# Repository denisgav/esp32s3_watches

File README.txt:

useful links:
https://mischianti.org/vcc-gnd-studio-yd-esp32-s3-devkitc-1-clone-high-resolution-pinout-and-specs/
https://github.com/rtek1000/YD-ESP32-23

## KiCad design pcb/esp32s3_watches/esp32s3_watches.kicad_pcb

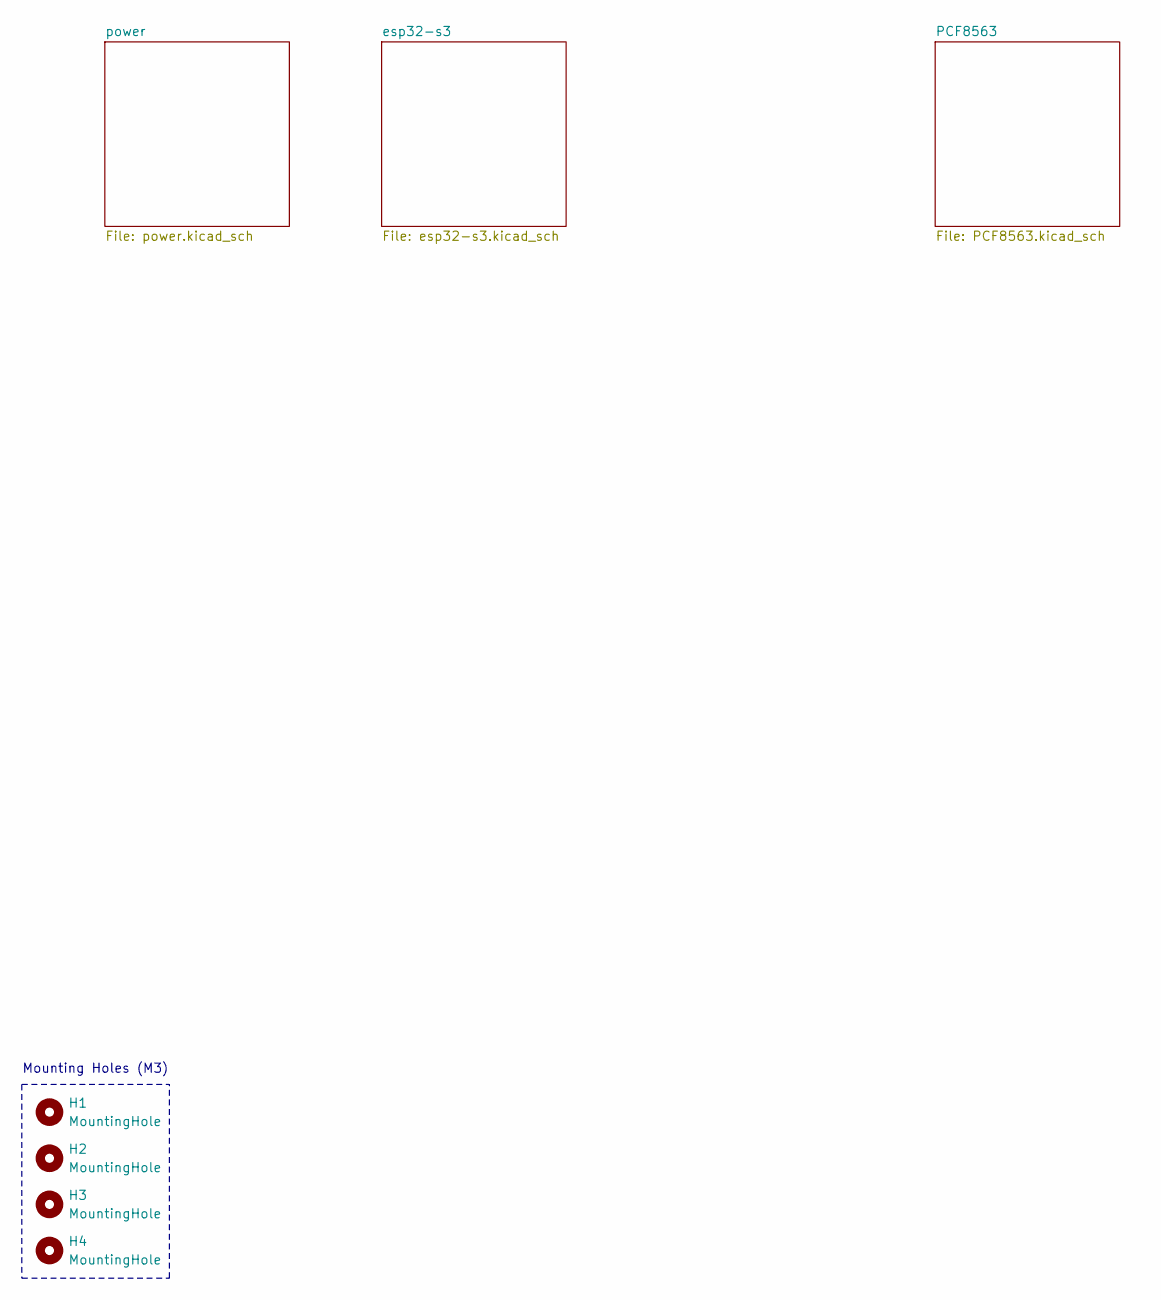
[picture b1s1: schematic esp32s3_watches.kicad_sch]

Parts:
H1, H2, H3, H4: MountingHole; MountingHole_3.2mm_M3

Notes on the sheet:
Mounting Holes (M3)

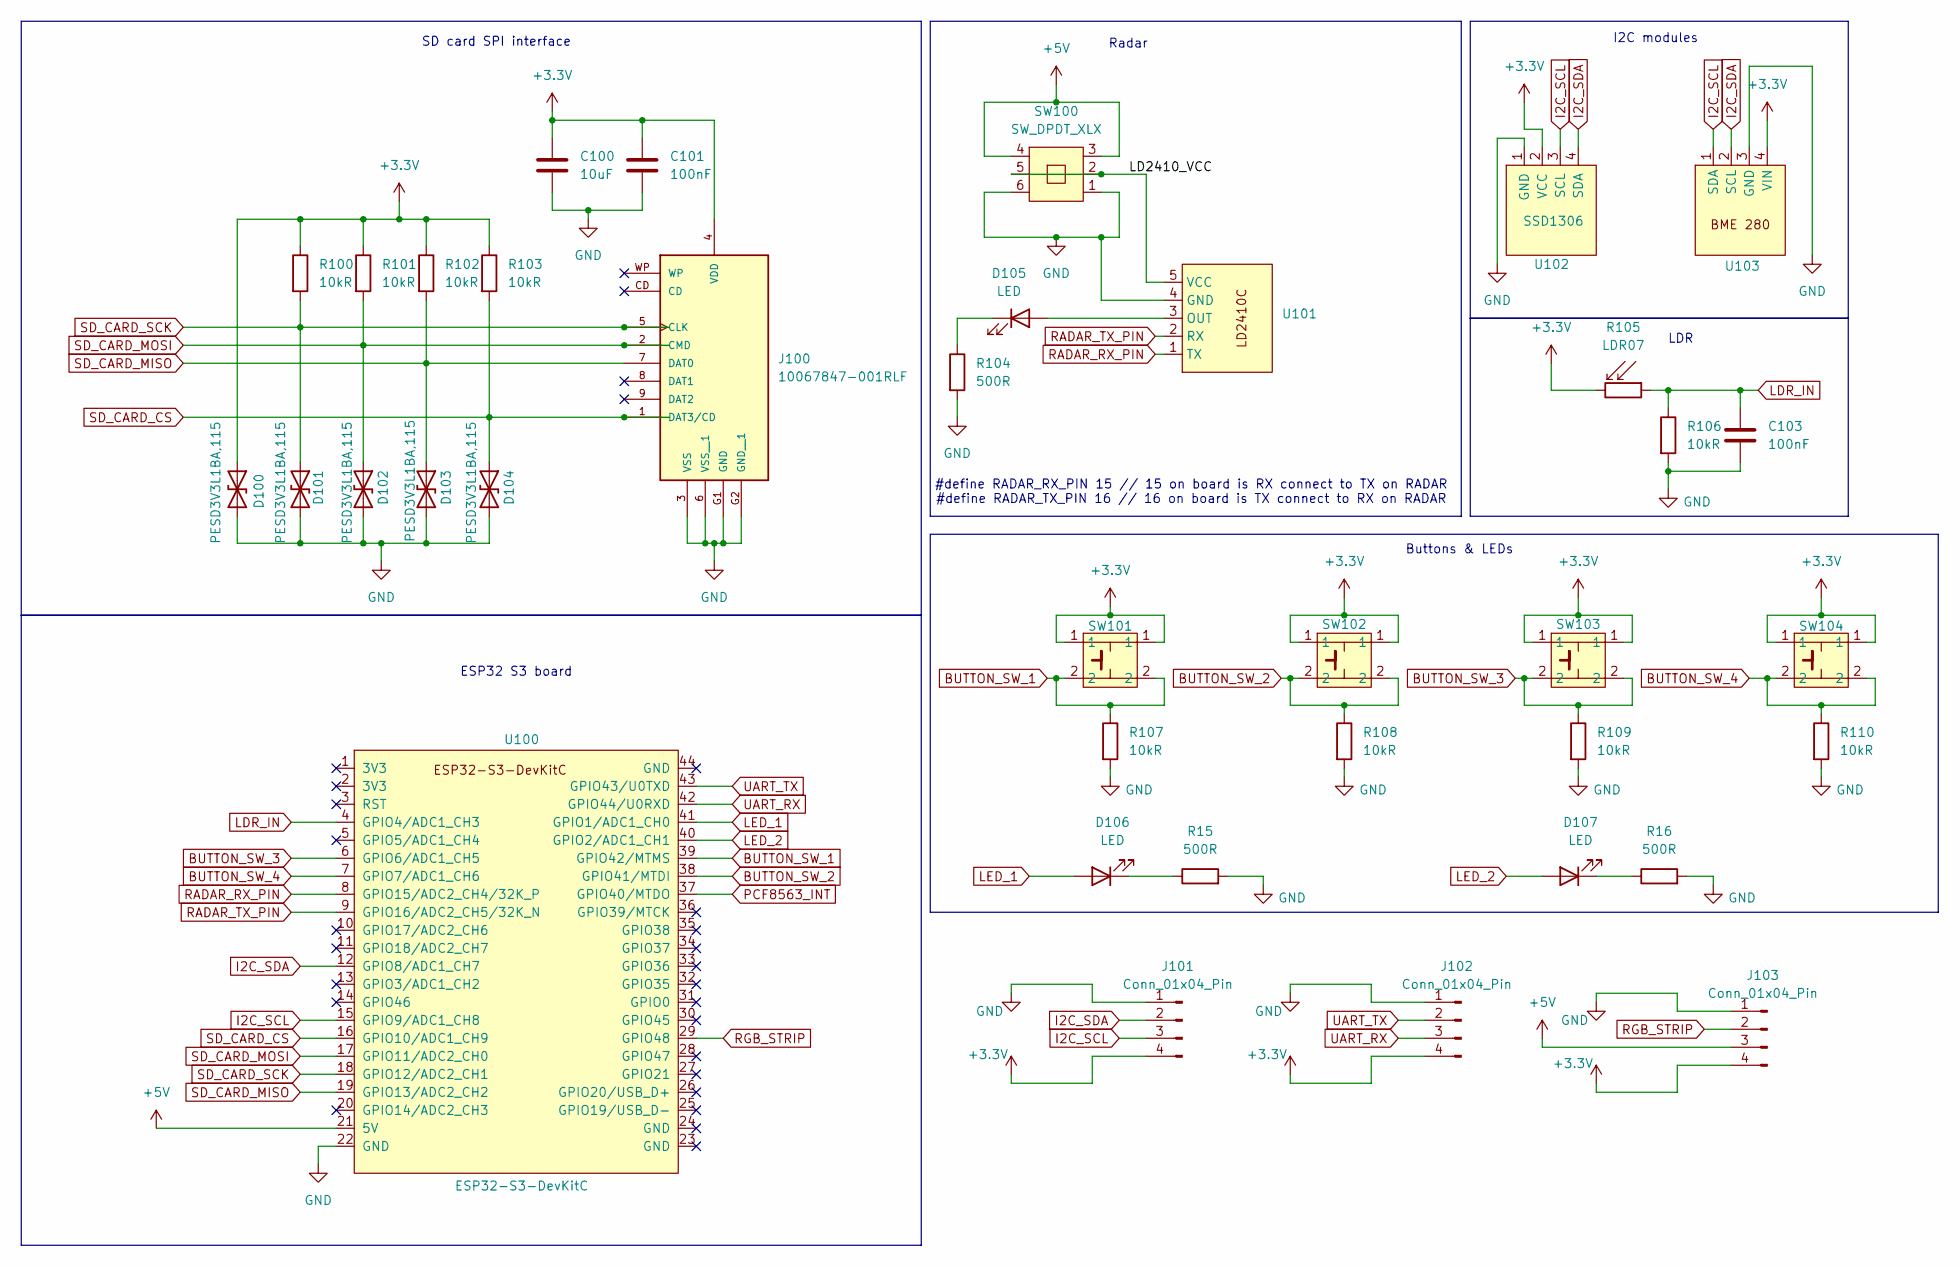
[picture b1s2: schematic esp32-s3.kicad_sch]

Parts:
C100: 10uF; C_0805_2012Metric
C101, C103: 100nF; C_0603_1608Metric
D100, D101, D102, D103, D104: PESD3V3L1BA,115; D_SOD-323; DigiKey Part Number 1727-3825-6-ND
D105, D106, D107: LED; LED_D5.0mm
J100: 10067847-001RLF; AMPHENOL_10067847-001RLF; PARTREV K
J101, J102, J103: Conn_01x04_Pin; PinHeader_1x04_P2.54mm_Vertical
R15, R16, R104: 500R; R_0805_2012Metric
R100, R101, R102, R103, R106, R107, R108, R109, R110: 10kR; R_0805_2012Metric
R105: LDR07; R_LDR_5.1x4.3mm_P3.4mm_Vertical
SW100: SW_DPDT_XLX
SW101, SW102, SW103, SW104: SW_PUSH_6mm_H5mm
U100: ESP32-S3-DevKitC
U101: LD2410C
U102: SSD1306; 128x64OLED
U103: BME280

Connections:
+3.3V: C100.1, C101.1, D100.1 (A1), J100.4 (VDD), J101.4, J102.4, J103.4, R100.1, R101.1, R102.1, R103.1, R105.2, SW101.1, SW102.1, SW103.1, SW104.1, U102.2 (VCC), U103.4 (VIN); also elsewhere on the board
+5V: J103.3, SW100.3, SW100.4, U100.21 (5V); also elsewhere on the board
/esp32-s3/LD2410_VCC: SW100.2, SW100.5, U101.5 (VCC)
BUTTON_SW_1: R107.1, SW101.2, U100.39 (GPIO42/MTMS)
BUTTON_SW_2: R108.1, SW102.2, U100.38 (GPIO41/MTDI)
BUTTON_SW_3: R109.1, SW103.2, U100.6 (GPIO6/ADC1_CH5)
BUTTON_SW_4: R110.1, SW104.2, U100.7 (GPIO7/ADC1_CH6)
GND: C100.2, C101.2, C103.2, D100.2 (A2), D101.2 (A2), D102.2 (A2), D103.2 (A2), D104.2 (A2), J100.3 (VSS), J100.6 (VSS__1), J100.G1 (GND), J100.G2 (GND__1), J101.1, J102.1, J103.1, R15.2, R16.2, R104.2, R106.2, R107.2, R108.2, R109.2, R110.2, SW100.1, SW100.6, U100.22 (GND), U101.4 (GND), U102.1 (GND), U103.3 (GND); also elsewhere on the board
I2C_SCL: J101.3, U100.15 (GPIO9/ADC1_CH8), U102.3 (SCL), U103.1 (SDA); also elsewhere on the board
I2C_SDA: J101.2, U100.12 (GPIO8/ADC1_CH7), U102.4 (SDA), U103.2 (SCL); also elsewhere on the board
LDR_IN: C103.1, R105.1, R106.1, U100.4 (GPIO4/ADC1_CH3)
LED_1: D106.2 (A), U100.41 (GPIO1/ADC1_CH0)
LED_2: D107.2 (A), U100.40 (GPIO2/ADC1_CH1)
unnamed: D105.2 (A), U101.3 (OUT)
unnamed: D105.1 (K), R104.1
unnamed: D106.1 (K), R15.1
unnamed: D107.1 (K), R16.1
PCF8563_INT: U100.37 (GPIO40/MTDO); also elsewhere on the board
RADAR_RX_PIN: U100.8 (GPIO15/ADC2_CH4/32K_P), U101.1 (TX)
RADAR_TX_PIN: U100.9 (GPIO16/ADC2_CH5/32K_N), U101.2 (RX)
RGB_STRIP: J103.2, U100.29 (GPIO48)
SD_CARD_CS: D104.1 (A1), J100.1 (DAT3/CD), R103.2, U100.16 (GPIO10/ADC1_CH9)
SD_CARD_MISO: D103.1 (A1), J100.7 (DAT0), R102.2, U100.19 (GPIO13/ADC2_CH2)
SD_CARD_MOSI: D102.1 (A1), J100.2 (CMD), R101.2, U100.17 (GPIO11/ADC2_CH0)
SD_CARD_SCK: D101.1 (A1), J100.5 (CLK), R100.2, U100.18 (GPIO12/ADC2_CH1)
UART_RX: J102.3, U100.42 (GPIO44/U0RXD)
UART_TX: J102.2, U100.43 (GPIO43/U0TXD)

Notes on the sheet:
ESP32 S3 board
I2C modules
Radar
Buttons & LEDs
LDR
SD card SPI interface
#define RADAR_RX_PIN 15 // 15 on board is RX connect to TX on RADAR #define RADAR_TX_PIN 16 // 16 on board is TX connect to RX on RADAR

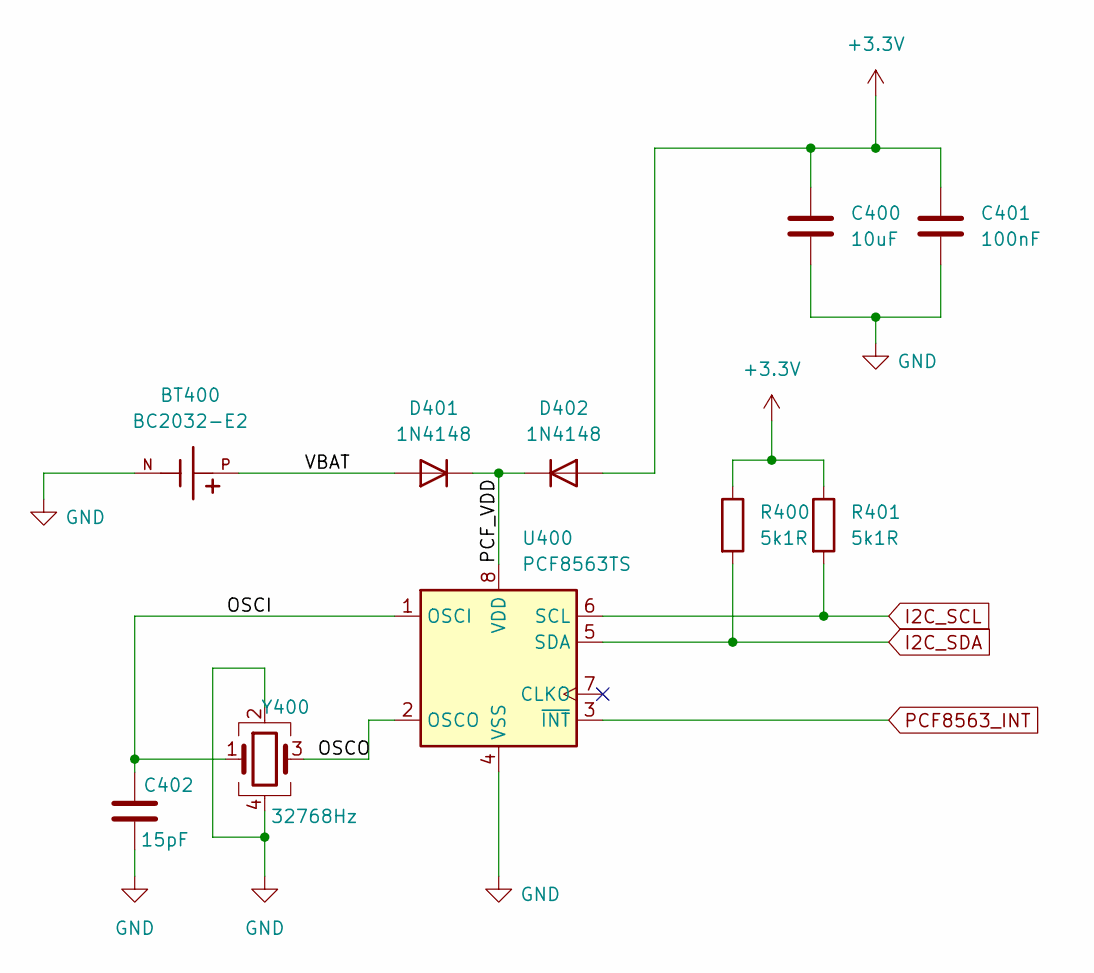
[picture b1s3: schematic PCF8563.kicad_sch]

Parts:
BT400: BC2032-E2; MPD_BC2032-E2; PARTREV D
C400: 10uF; C_0805_2012Metric
C401: 100nF; C_0603_1608Metric
C402: 15pF; C_0603_1608Metric; DigiKey Part Number 490-11191-6-ND
D401, D402: 1N4148; D_SOD-123
R400, R401: 5k1R; R_0805_2012Metric
U400: PCF8563TS; MSOP-8_3x3mm_P0.65mm
Y400: 32768Hz; Crystal_SMD_3225-4Pin_3.2x2.5mm; DigiKey Part Number 535-ASEK-32.768KHZ-L-R-TDKR-ND

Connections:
+3.3V: C400.1, C401.1, D402.2 (A), R400.1, R401.1; also elsewhere on the board
/PCF8563/OSCI: C402.1, U400.1 (OSCI), Y400.1
/PCF8563/OSCO: U400.2 (OSCO), Y400.3
/PCF8563/PCF_VDD: D401.1 (K), D402.1 (K), U400.8 (VDD)
/PCF8563/VBAT: BT400.P, D401.2 (A)
GND: BT400.N, C400.2, C401.2, C402.2, U400.4 (VSS), Y400.2, Y400.4; also elsewhere on the board
I2C_SCL: R401.2, U400.6 (SCL); also elsewhere on the board
I2C_SDA: R400.2, U400.5 (SDA); also elsewhere on the board
PCF8563_INT: U400.3 (~INT); also elsewhere on the board

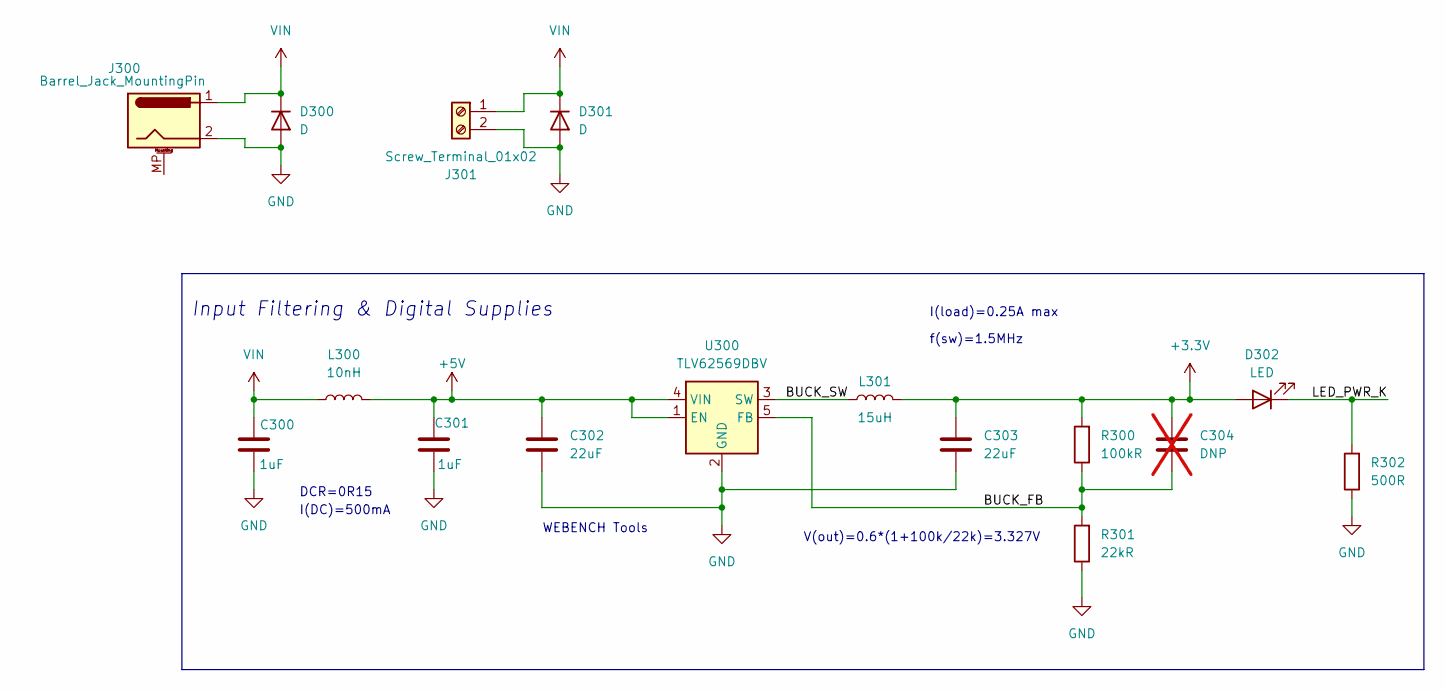
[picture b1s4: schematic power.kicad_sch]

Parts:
C300, C301: 1uF; C_0805_2012Metric; DigiKey Part Number 1276-1946-6-ND
C302, C303: 22uF; C_0805_2012Metric; DigiKey Part Number 1276-6687-6-ND
C304: DNP; C_0603_1608Metric; not fitted
D300, D301: D; D_PowerDI-123; Part Number SBR3M30P1-7
D302: LED; LED_D5.0mm; DigiKey Part Number 732-4971-6-ND
J300: Barrel_Jack_MountingPin; BarrelJack_GCT_DCJ200-10-A_Horizontal; Part Number DC-005-A200
J301: Screw_Terminal_01x02; terminal_block; Part Number WJ500V-5.08-2P
L300: 10nH; L_0603_1608Metric; DigiKey Part Number 712-LRC0402CJ10NGV001TDKR-ND
L301: 15uH; MWSA0603S; DigiKey Part Number 3442-MWSA0603S-150MTDKR-ND
R300: 100kR; R_0805_2012Metric; DigiKey Part Number P100KLDKR-ND
R301: 22kR; R_0805_2012Metric; DigiKey Part Number P22.0KLDKR-ND
R302: 500R; R_0805_2012Metric; DigiKey Part Number P1.00KLDKR-ND
U300: TLV62569DBV; SOT-23-5; DigiKey Part Number 296-47360-6-ND

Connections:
+3.3V: C303.1, C304.1, D302.2 (A), L301.2, R300.2; also elsewhere on the board
+5V: C301.1, C302.1, L300.2, U300.1 (EN), U300.4 (VIN); also elsewhere on the board
/power/BUCK_FB: C304.2, R300.1, R301.2, U300.5 (FB)
/power/BUCK_SW: L301.1, U300.3 (SW)
/power/LED_PWR_K: D302.1 (K), R302.2
GND: C300.2, C301.2, C302.2, C303.2, D300.2 (A), D301.2 (A), J300.2, J301.2, R301.1, R302.1, U300.2 (GND); also elsewhere on the board
VIN: C300.1, D300.1 (K), D301.1 (K), J300.1, J301.1, L300.1

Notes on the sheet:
V(out)=0.6*(1+100k/22k)=3.327V
DCR=0R15
f(sw)=1.5MHz
I(load)=0.25A max
Input Filtering & Digital Supplies
I(DC)=500mA
WEBENCH Tools

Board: 2 copper layers, 67 parts (1 on the bottom side), 35 nets, no tracks yet.

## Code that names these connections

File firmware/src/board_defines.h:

#pragma once

// SD CARD
#define SD_CARD_MISO 13
#define SD_CARD_SCK  12
#define SD_CARD_MOSI 11
#define SD_CARD_CS   10

// Buttons
#define BUTTON_SW_1 6
#define BUTTON_SW_2 7
#define BUTTON_SW_3 42
#define BUTTON_SW_4 41

// LEDS
#define LED_1 1
#define LED_2 2

// LDR
#define LDR_IN 4

//I2C
#define I2C_SDA 8
#define I2C_SCL 9

#define I2C_BME280_ADDRESS 0x76

// LED strip
// How many leds in your strip?
// #define WS2812_ONBOARD_NUM_LEDS 1
// #define WS2812_ONBOARD_LED_PIN 48
#define WS2812_CLOCK_NUM_LEDS 60
#define WS2812_CLOCK_LED_PIN 48

// SSD 1306
#define SSD1306_SCREEN_WIDTH   128 // OLED display width, in pixels
#define SSD1306_SCREEN_HEIGHT  64 // OLED display height, in pixels
#define SSD1306_OLED_RESET     -1 // Reset pin # (or -1 if sharing Arduino reset pin)
#define SSD1306_SCREEN_ADDRESS 0x3c ///< See datasheet for Address; 0x3D for 128x64, 0x3C for 128x32

// Radar
#define MONITOR_SERIAL Serial
#define RADAR_SERIAL Serial1
#define RADAR_RX_PIN 15 // 15 on board is RX connect to TX on RADAR
#define RADAR_TX_PIN 16 // 16 on board is TX connect to RX on RADAR

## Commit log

2025-02-12 Initial firmware
2025-02-12 Add sensor LD2410
2025-02-14 Update SD card connection
2025-02-14 Scheme improvements
2025-02-15 BOM file updates. Scheme complete.
2025-02-15 PCB initial layout
2025-02-16 Components can not fit 10x10 board
2025-02-16 minor PCB updates
2025-02-16 Split scheme to 2 boards
